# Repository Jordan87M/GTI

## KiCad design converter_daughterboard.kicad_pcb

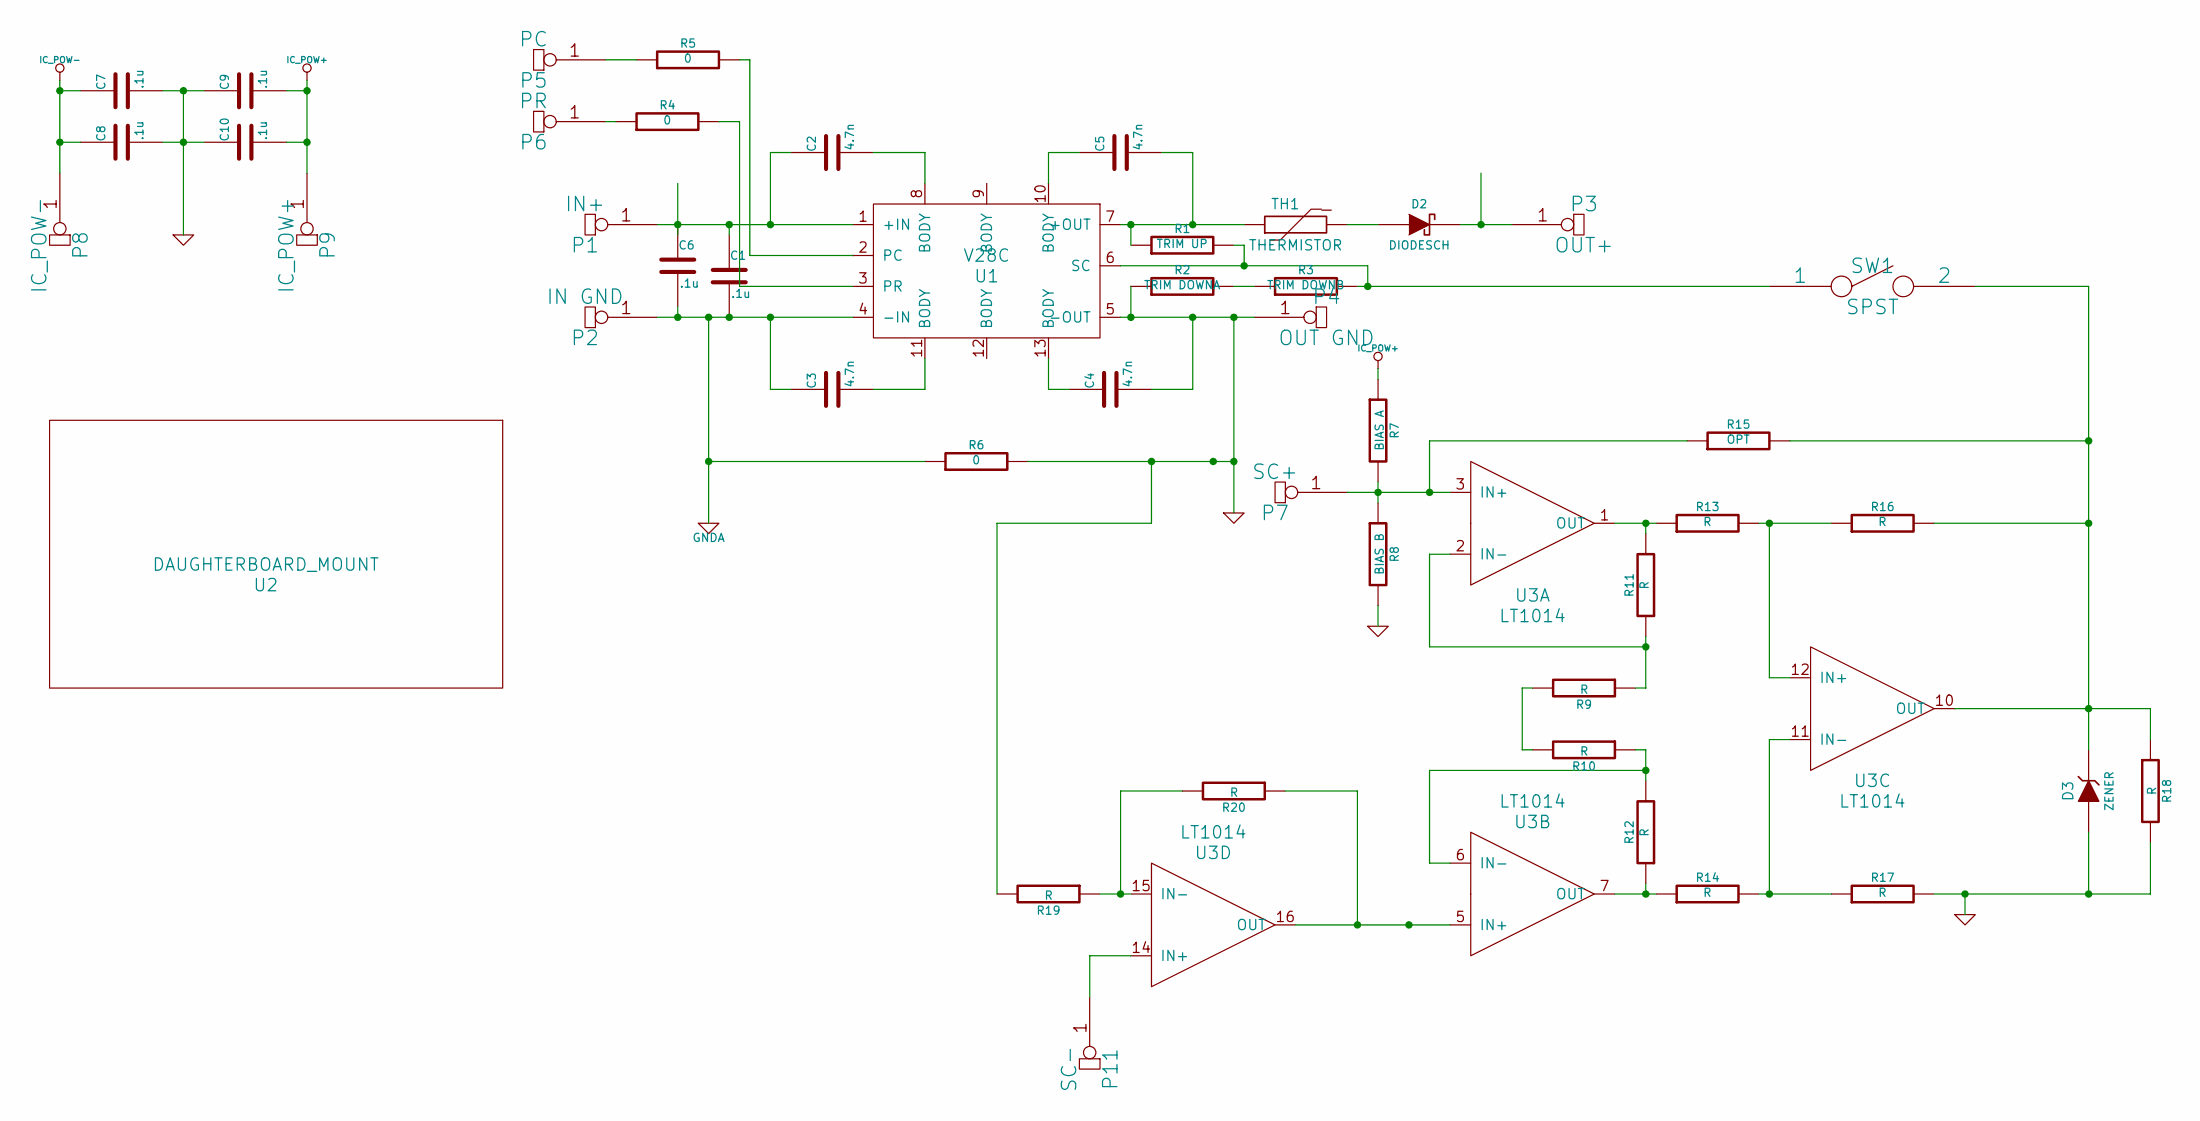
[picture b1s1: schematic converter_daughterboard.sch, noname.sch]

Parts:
C1, C6, C7, C8, C9, C10: .1u
C2, C3, C4, C5: 4.7n
D2: DIODESCH
D3: ZENER
P1: IN+
P2: IN GND
P3: OUT+
P4: OUT GND
P5: PC
P6: PR
P7: SC+
P8: IC_POW-
P9: IC_POW+
P11: SC-
R1: TRIM UP
R2: TRIM DOWNA
R3: TRIM DOWNB
R4, R5, R6: 0
R7: BIAS A
R8: BIAS B
R9, R10, R11, R12, R13, R14, R16, R17, R18, R19, R20: R
R15: OPT
SW1: SPST
TH1: THERMISTOR
U1: V28C
U2: DAUGHTERBOARD_MOUNT
U3: LT1014

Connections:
GND: C4.2, C7.2, C8.2, C9.1, C10.1, D3.1 (A), P4.1, R2.1, R6.2, R8.2, R17.2, R18.2, R19.2, U1.5 (-OUT)
GNDA: C1.2, C3.1, C6.2, P2.1, R6.1, U1.4 (-IN)
IC_POW+: C9.2, C10.2, P9.1, R7.1, U3.4 (IC_POW+)
IC_POW-: C7.1, C8.1, P8.1, U3.13 (IC_POW-)
unnamed: R14.2, R17.1, U3.11 (IN-)
unnamed: R11.2, R13.1, U3.1 (OUT)
unnamed: R9.1, R11.1, U3.2 (IN-)
unnamed: R10.1, R12.2, U3.6 (IN-)
unnamed: R12.1, R14.1, U3.7 (OUT)
unnamed: R9.2, R10.2
unnamed: R13.2, R16.1, U3.12 (IN+)
unnamed: D3.2 (K), R15.2, R16.2, R18.1, SW1.2, U3.10 (OUT)
unnamed: R19.1, R20.2, U3.15 (IN-)
unnamed: P11.1, U3.14 (IN+)
unnamed: P7.1, R7.2, R8.1, R15.1, U3.3 (IN+)
unnamed: R20.1, U3.5 (IN+), U3.16 (OUT)
unnamed: C3.2, U1.11 (BODY)
unnamed: C2.2, U1.8 (BODY)
unnamed: C4.1, U1.13 (BODY)
unnamed: R1.2, R3.2, SW1.1, U1.6 (SC)
unnamed: R2.2, R3.1
unnamed: C5.1, U1.10 (BODY)
unnamed: C5.2, R1.1, TH1.1, U1.7 (+OUT)
unnamed: R4.2, U1.3 (PR)
unnamed: R5.2, U1.2 (PC)
unnamed: P5.1, R5.1
unnamed: P6.1, R4.1
unnamed: D2.1 (A), TH1.2
unnamed: D2.2 (K), P3.1
unnamed: C1.1, C2.1, C6.1, P1.1, U1.1 (+IN)

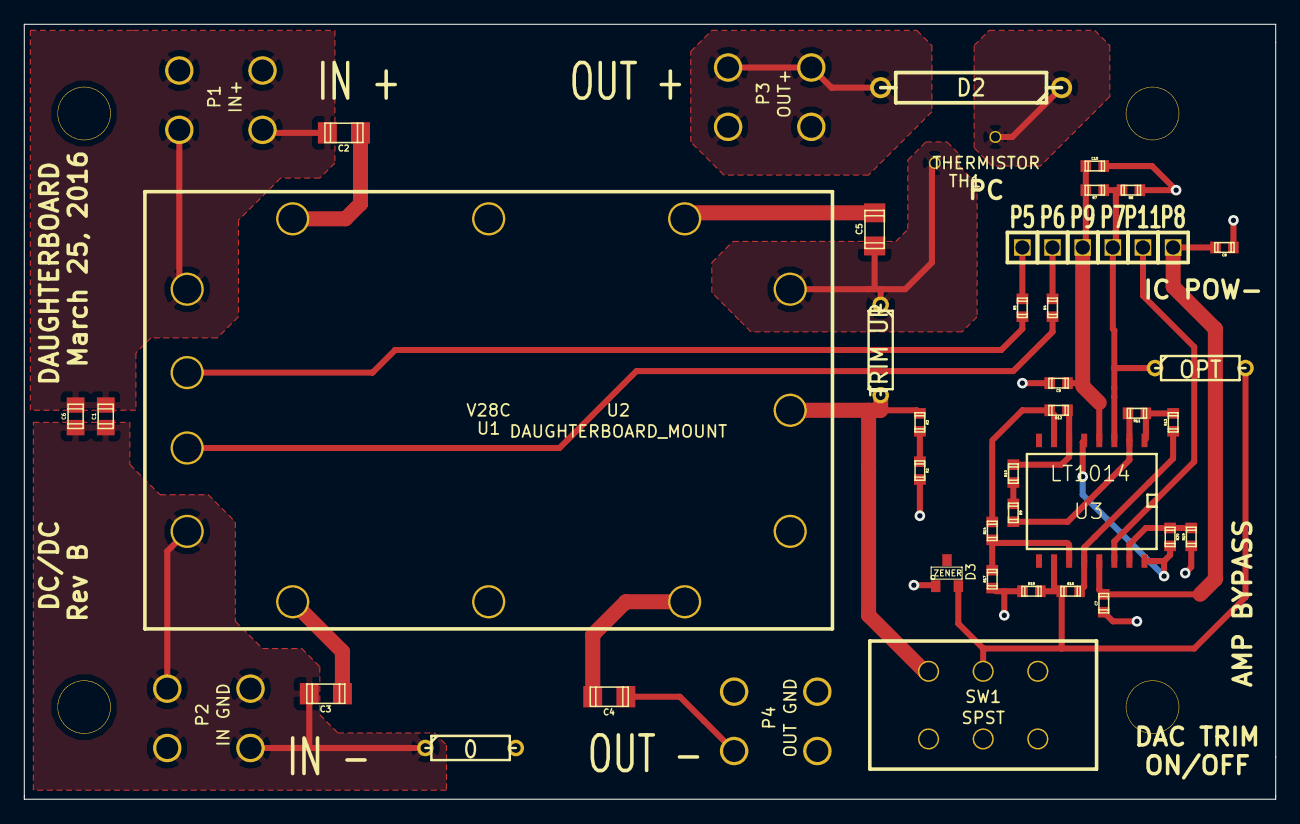
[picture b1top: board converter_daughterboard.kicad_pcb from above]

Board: 2 copper layers, 105.4 x 65.3 mm, 47 parts (0 on the bottom side), 30 nets.

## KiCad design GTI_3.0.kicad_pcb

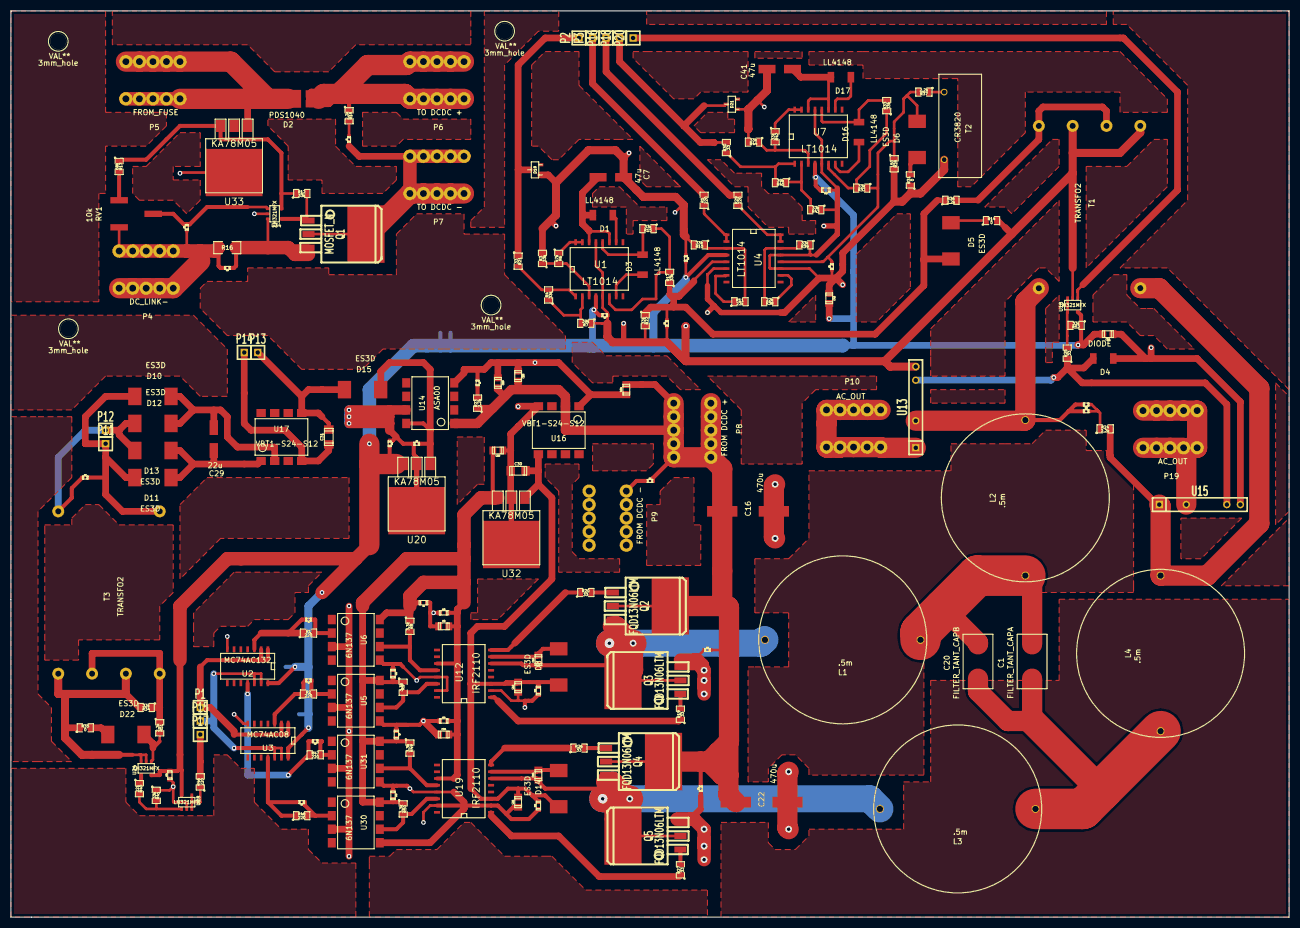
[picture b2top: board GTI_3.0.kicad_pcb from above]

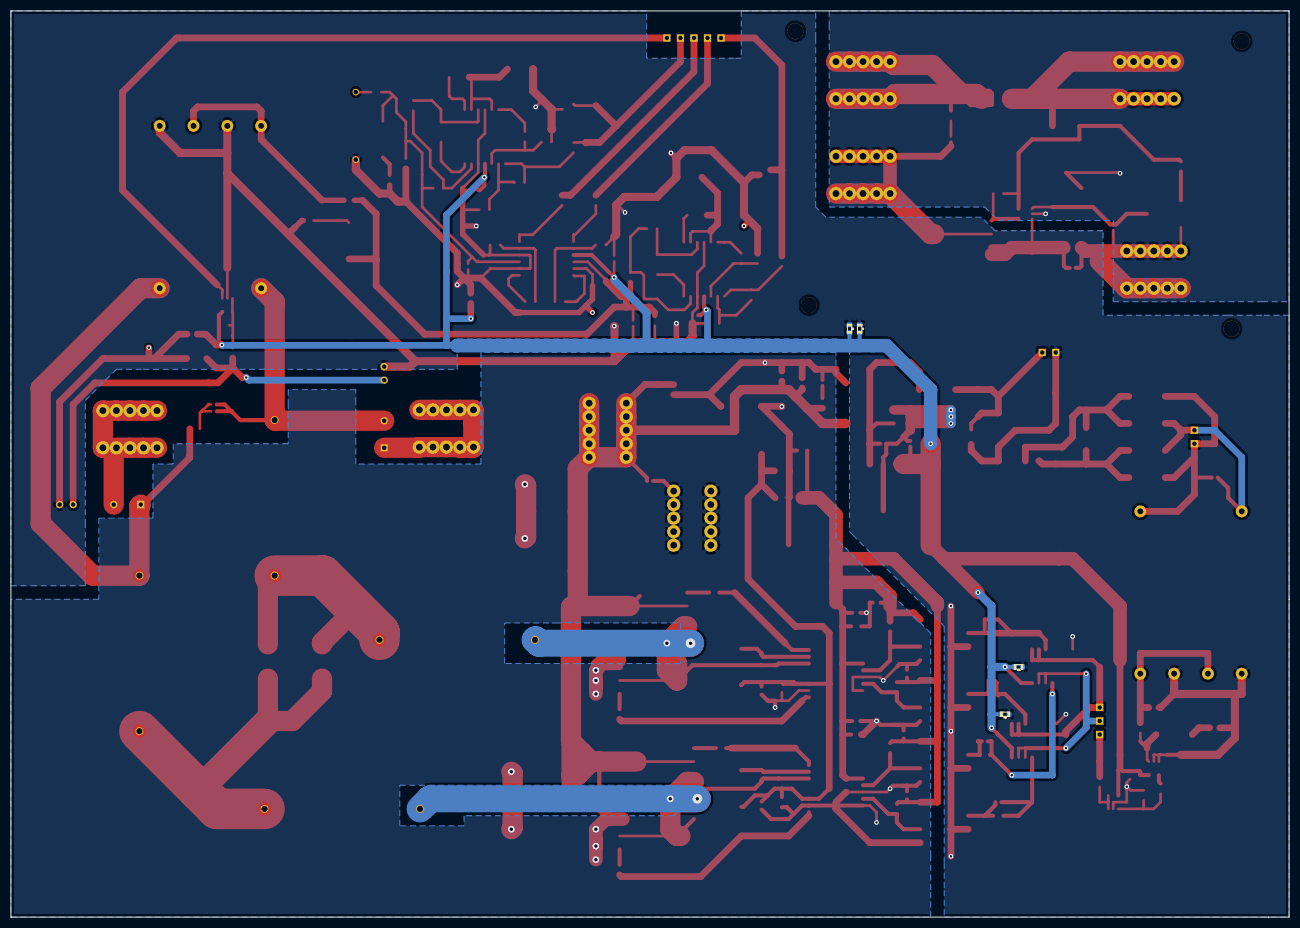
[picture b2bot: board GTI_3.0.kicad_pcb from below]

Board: 2 copper layers, 240.0 x 170.2 mm, 185 parts (4 on the bottom side), 98 nets.

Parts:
3mm_hole, 3mm_hole#2, 3mm_hole#3, 3mm_hole#4: VAL**; 3mm_hole
C1: FILTER_TANT_CAPA; 7343-31
C2, C3, C46, C47: 1n; c_0402
C4, C5, C6, C8, C10, C15, C25, C35, C42, C43, C44, C48, C49, C51: .1u; c_0603
C7, C41: 47u; PANASONIC_SMT_CAP_D
C9, C13, C14, C19, C23, C24, C26, C28, C33, C36, C45, C54: .47u; c_0805
C12, C34, C37: 10n; c_0402
C16, C22: 470u; PANASONIC_SMT_CAP_H
C17, C18, C21, C27, C32, C40, C50, C52, C53: .1u; c_0402
C20: FILTER_TANT_CAPB; 7343-31
C29: 22u; PANASONIC_SMT_CAP_C
C30, C31: .33u; c_1206
D1, D3, D16, D17: LL4148; SOD-80
D2: PDS1040; POWERDI5
D4: DIODE; SOD-80
D5, D6, D8, D10, D11, D12, D13, D14, D15, D22: ES3D; SMC
D7, D9, D19, D20: LNJ247W82RA; c_0402
D18, D21: BZX84C3V3; sot23
L1, L2, L3, L4: .5m; Bourns_High_Current_Choke
P1: HIGH_FREQ_PWM; SIL-1
P2: OUTPUTV_PEAK; SIL-1
P3: OUTPUTV_EDGE_DET; SIL-1
P4: DC_LINK-; Screw_TerminalA
P5: FROM_FUSE; Screw_TerminalA
P6: TO DCDC +; Screw_TerminalA
P7: TO DCDC -; Screw_TerminalA
P8: FROM DCDC +; Screw_TerminalA
P9: FROM DCDC -; Screw_TerminalA
P10, P19: AC_OUT; Screw_TerminalA
P11: GRID REF +; SIL-1
P12: GRID REF -; SIL-1
P13: EVK_POW+; SIL-1
P14: EVK_POW-; SIL-1
P15: LOW_FREQ_PWM; SIL-1
P16: OUTPUTI_EDGE_DET; SIL-1
P17: REF_EDGE_DET; SIL-1
P18: OUTPUTI_PEAK; SIL-1
P20: DIS/CONN; SIL-1
Q1: MOSFET_N; TO263
Q2, Q3, Q4, Q5: FQD13N06LTM; TO263
R1, R2, R5, R29, R46, R47, R48: 220; SM0805
R3, R4, R10, R12, R15, R17, R22, R32, R33, R34, R39, R41, R42, R43, R44, R52: 33k; SM0805
R6: 47k; SM0805
R7, R45: 39k; SM0805
R8, R9, R49, R50: 3.3k; SM0805
R11, R38, R40: 22k; SM0805
R13: 68k; SM0805
R14, R31, R35: 0; SM0805
R16: .01; SM1206
R18, R23, R24, R36, R37, R51: 2.2k; SM0805
R19, R20, R21, R25, R26, R27, R30: 33; SM0805
R28: 150; SM0805
RV1: 10k; Bourns_3361
T1, T3: TRANSFO2; Tamura_3FS
T2: CR3820; CR3800_XFMR
U1, U4, U7: LT1014; SO16W
U2: MC74AC132; SO14N
U3: MC74AC08; SO14N
U5, U6, U30, U31: 6N137; 8-DIP_SMT
U12, U19: IRF2110; SO16W
U13, U15: SSR; SSRfromSIL7
U14: ASA00; 8-DIP_SMT
U16, U17: VBT1-S24-S12; 8-DIP_SMT
U18, U24, U28, U34: LM321MFX; SOT23-5
U20, U32, U33: KA78M05; DPAK3

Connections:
+5V: C4.1, C5.1, C9.1, C10.1, C33.1, C35.1, C36.1, C48.1, C49.1, R8.1, R9.1, R49.1, R50.1, U5.8, U6.8, U12.11, U19.11, U30.8, U31.8, U32.3
+5VA: C6.1, C8.1, C32.1, C40.1, C42.1, C43.1, C44.1, C45.1, C50.1, C51.1, C54.1, R52.1, U1.4, U2.14, U3.14, U4.4, U7.4, U18.5, U20.3, U24.5, U28.5
+12V: C14.1, C15.1, C25.1, C26.1, C27.1, C30.1, C31.1, D8.1, D14.1, D15.1, D15.2, P13.1, U12.3, U14.8, U16.5, U17.5, U19.3, U20.1, U32.1
+24V: C16.1, C17.1, C18.1, C19.1, C21.1, C22.1, C23.1, C24.1, P8.1, Q2.2, Q4.2, R23.1, U14.1, U16.2
/DClinkGND: C53.2, Q1.3, R16.2, U34.3
GND: C4.2, C5.2, C9.2, C10.2, C14.2, C15.2, C16.2, C17.2, C18.2, C19.2, C21.2, C22.2, C23.2, C24.2, C25.2, C26.2, C30.2, C33.2, C35.2, C36.2, C48.2, C49.2, D9.2, P9.1, Q3.3, Q5.3, U5.5, U6.5, U12.2, U12.13, U12.15, U14.4, U16.1, U16.4, U19.2, U19.13, U19.15, U30.5, U31.5, U32.2
GNDA: C6.2, C7.2, C8.2, C12.2, C27.2, C31.2, C32.2, C34.2, C40.2, C41.2, C42.2, C43.2, C44.2, C45.2, C50.2, C51.2, C54.2, D4.1, D18.1, D21.1, P14.1, R3.2, R7.1, R10.2, R14.2, R22.2, R28.2, R31.1, R34.2, R35.1, R39.1, R41.1, R43.1, R44.2, T1.6, T1.8, T2.2, T3.6, T3.8, U1.5, U1.13, U2.7, U3.7, U4.6, U4.11, U4.13, U5.3, U6.3, U7.5, U7.13, U13.7, U14.7, U15.7, U17.4, U18.2, U20.2, U24.2, U24.3, U28.2, U30.3, U31.3
unnamed: Q4.1, R26.2
unnamed: Q5.1, R27.2
unnamed: Q3.1, R19.2
unnamed: Q2.1, R20.2
unnamed: R8.2, U6.6, U12.12
unnamed: R9.2, U5.6, U12.14
unnamed: C29.1, D10.2, D12.2, U17.2
unnamed: D1.1, U1.10
unnamed: R29.1, U4.15, U4.16
unnamed: R46.1, U28.3, U28.4
unnamed: R40.1, U24.4
unnamed: R40.2, R41.2, U28.1
unnamed: R11.1, U4.7
unnamed: R38.2, R39.2, U4.14
unnamed: R38.1, U4.10
unnamed: R43.2, R45.1, U7.2
unnamed: C29.2, D11.1, D13.1, U17.1
unnamed: R32.2, R33.1, U7.6
unnamed: R49.2, U19.12, U31.6
unnamed: R20.1, U12.8
unnamed: R19.1, U12.1
unnamed: R50.2, U19.14, U30.6
unnamed: R26.1, U19.8
unnamed: R27.1, U19.1
unnamed: R5.1, U4.1, U4.2
unnamed: D3.1, U1.7
unnamed: P3.1, R5.2
unnamed: P17.1, R46.2
unnamed: D7.2, P7.1, Q1.2
unnamed: D7.1, R18.2
unnamed: D2.2, P6.1, R18.1
unnamed: D9.1, R23.2
unnamed: R4.2, R21.2, U1.1
unnamed: R3.1, R6.2, U1.3
unnamed: P19.1, U15.3
unnamed: P10.1, U13.1
unnamed: R4.1, R7.2, U1.2
unnamed: Q1.1, R12.2, U34.4
unnamed: R36.2, T1.5, T1.7
unnamed: R30.1, R45.2, U7.1
unnamed: R42.2, R44.1, U7.3
unnamed: D17.1, U7.10
unnamed: R6.1, U1.15, U1.16
unnamed: C7.1, D1.2, U1.11, U1.14
unnamed: D3.2, R15.2, U1.12
unnamed: R15.1, R17.2, U1.6
unnamed: D5.1, R14.1
unnamed: D22.2, R51.2, U24.1
unnamed: D6.1, R31.2
unnamed: R37.1, T2.1
unnamed: C12.1, D5.2, R17.1, R22.1, R36.1, U4.5
unnamed: D22.1, R35.2
unnamed: R34.1, R51.1, T3.5, T3.7
unnamed: R25.2, R52.2, U18.3, U18.4
unnamed: P20.1, U18.1
unnamed: C34.1, D6.2, R28.1, R32.1, R37.2, U4.12
unnamed: R13.2, RV1.1
unnamed: D21.2, P18.1, R30.2
unnamed: P16.1, R29.2
unnamed: D18.2, P2.1, R21.1
unnamed: D19.1, D20.2, L2.2, T1.1, U13.3
unnamed: C1.1, C20.1, L1.1, L2.1
unnamed: C1.2, C20.2, L3.1, L4.1
unnamed: L4.2, R24.2, T1.4, U15.1
unnamed: C41.1, D17.2, U7.11, U7.14
unnamed: D16.2, R33.2, U7.12
unnamed: D16.1, U7.7
unnamed: R42.1, U7.15, U7.16
unnamed: C52.1, RV1.2, U34.1
unnamed: D4.2, R25.1, U13.6, U15.6
unnamed: C52.2, C53.1, P4.1, R16.1, RV1.3, U33.2, U34.2
unnamed: R12.1, R13.1, U33.3, U34.5
unnamed: D2.1, P5.1, U33.1
unnamed: P15.1, U2.12, U2.13, U3.12, U3.13
unnamed: P1.1, U2.1, U2.2, U3.1, U3.2
unnamed: C13.2, L1.2, Q2.3, Q3.2, U12.6
unnamed: C28.2, L3.2, Q4.3, Q5.2, U19.6
unnamed: R10.1, R11.2, U4.3
unnamed: C28.1, D14.2, U19.7
unnamed: C13.1, D8.2, U12.7
unnamed: C47.2, R48.2, U30.2
unnamed: C37.2, D12.1, D13.2, P12.1, T3.4
unnamed: C37.1, D10.1, D11.2, P11.1, T3.1
unnamed: C3.2, R2.2, U5.2
unnamed: C46.2, R47.2, U31.2
unnamed: C46.1, R47.1, U2.11
unnamed: C2.2, R1.2, U6.2
unnamed: C2.1, R1.1, U2.3
unnamed: C3.1, R2.1, U3.3
unnamed: C47.1, R48.1, U3.11
unnamed: D19.2, D20.1, R24.1

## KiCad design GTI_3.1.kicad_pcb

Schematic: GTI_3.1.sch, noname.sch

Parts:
C1, C2, C13, C20, C117: 22p
C3, C4, C10, C11, C15, C16, C19, C23, C31, C44, C103, C104, C105, C106: 33n
C5, C56, C87: 4.7u
C6, C7, C21, C113: 2.2u
C8, C12, C14, C17, C22, C24, C25, C26, C30, C32, C34, C37, C39, C40, C42, C48, C49, C50, C51, C54, C57, C61, C64, C68, C72, C82, C86, C89, C91, C92, C93, C94, C97, C98, C107, C108, C109, C110, C111, C118, C120, C121, C122, C123, C124, C125: .1u
C9: 470p
C18, C99, C100, C101, C102: 2.7n
C27: 22u
C28, C59, C60, C65, C74, C76, C80, C83, C84: .47u
C29, C58, C85, C88, C116: 10n
C33, C52, C90, C119: 47u
C35, C70, C73, C78, C79: 10u
C36, C38, C41, C43, C127: CSNUB
C45, C112: 1u
C46, C47, C95, C96: DNS
C53: CP1
C55: C
C62, C69: 470u
C63: 120u
C66, C67: NP_FILTER_CAP
C71, C77, C114, C115, C126, C128: 1n
C75: 100u
C81: .33u
D1: TVS
D2: MBRS340T3G
D3, D11, D22, D23, D24, D25: BZX84C3V3
D4, D20, D21: STPS1L20MF
D5, D7, D9, D10, D18, D19: LL4148
D6, D8, D12, D14: ES3D
L1: MSS1278 15u
L2, L3, L4, L5: .5m
L6: 4.7u
L7: 56uH
L8: 4.7uH
P1: PROGRAM_INT
P2: SPI1 SCK
P3: SPI1 MOSI
P4: SPI1 MISO
P5: SPI1_CS2
P6: HIGH_FREQ_PWM
P7: OUTPUTV_PEAK
P8: OUTPUTV_EDGE_DET
P9: FROM_FUSE
P10: DC_LINK-
P11: GNDB_TEST_#1
P12: BRD_DC_LINK+
P13: BRD_DC_LINK-
P14: TO DCDC +
P15: TO DCDC -
P16: FROM DCDC +
P17: FROM DCDC -
P18, P27: AC_OUT
P19: OUTPUT_INDICATOR_A
P20: BRD_DC_RAIL+
P21: BRD_DC_RAIL-
P22: OUTPUT_INDICATOR_B
P23: GRID REF +
P24: GRID REF -
P25: DIS/CONN OUT
P26: BRD_GRID_REF+
P28: DIS/CONN IN
P29: BRD_GRID_REF-
P30: DIS/CONN_TEST
P31: GNDA_TEST_#1
P32: LOW_FREQ_PWM
P33: OUTPUTI_EDGE_DET
P34: REF_EDGE_DET
P35: OUTPUTI_PEAK
P36: BACKLIGHT_5V
P37: 5V_SOURCE_RELAY_SUPPLY
P38: 5V_SOURCE_RELAY_RETURN
P39: RESET_N
P40: GNDA
P41: VCC3_3
P42: ALT_VOLTAGE_MEAS
P43: ALT_CURRENT_MEAS
P44: ALT_REF
P45: PWM_BRIGHTNESS
P46: ALT_MEAS_12VA
P47: ALT_MEAS_GNDA
P48, P49: CONNECTOR
Q1: DMN6075
Q2, Q3, Q4, Q5: FQD13N06LTM
R1, R41, R65, R67, R95: 10k
R2, R34, R35, R42, R45, R47, R51, R54, R58, R59, R61, R62, R64, R66, R68, R69, R71, R86, R88, R89, R90: 33k
R3, R8, R9, R12, R18, R19, R83: 2.2k
R4, R7, R17, R20: 1M
R5, R32, R33, R36, R70, R73, R75, R76: 220
R6: 1.5k
R10, R11, R13, R15: RSNUB
R14: 4.7k
R16, R57: 150
R21, R23: 4.7
R22: 18
R24, R25, R27, R30: 51
R26, R28, R29, R39, R40, R43, R44, R46, R60, R77, R78, R87: 3.3k
R31, R53, R74, R92: 33
R37, R98: 47k
R38, R72, R91: 39k
R48, R49, R55, R56, R96: 22
R50, R63: 1k
R52: MIN_LOAD
R79, R80: 39
R81, R82: 100
R84, R85: 56k
R93: 30k
R94: 330
R97: DNS
RV1: 10k
SW1: SPDT_RELAY
SW2: PANASONIC_DE2A-12V
T1, T3: TRANSFO2
T2: CR3820
TH1: PTC
U1: DAUGHTERBOARD_MOUNT
U2: AT32UC3A
U3: 50MHZCFPS73
U4: DP83848I
U5: LMS8117ADTX-3.3
U6: MICRO_USB_B
U7: LM2678SD-5.0
U8: J3026G01DNLT
U9: PQD6-Q24-D12
U10: LMT87
U11: MC74AC132
U12: MC74AC08
U13, U17, U20, U30: LT1014
U14, U15, U33, U34: 6N137
U16, U25, U31, U32: LM321MFX
U18: TLV3401
U19, U27: IRF2110
U21: MC74HC1G32
U22: PQMC1-S24-S12
U23: SN74AHC
U28, U29: KA78M05
VR1, VR2, VR3: VR
X1: CRYSTAL
X2: CRYSTAL_32K

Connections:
+5V: C48.1, C49.1, C56.1, C57.1, C83.1, C86.1, C87.1, C97.1, C98.1, R39.1, R40.1, R77.1, R78.1, U14.8 (Vcc), U15.8 (Vcc), U19.11 (Vdd), U27.11 (Vdd), U29.3 (OUT), U33.8 (Vcc), U34.8 (Vcc)
+5VA: C50.1, C80.1, C82.1, C84.1, C118.1, U10.1 (Vdd), U11.14 (+5VA), U12.14 (+5VA), U28.3 (OUT)
+12V: C60.1, C61.1, C72.1, C74.1, C75.1, D8.1 (A), D14.1 (A), R60.1, U19.3 (VCC), U22.6 (V_out_+), U27.3 (VCC), U29.1 (IN)
+12VA: C51.1, C54.1, C78.2, C89.1, C91.1, C92.1, C93.1, C94.1, C115.2, C120.1, C123.1, D6.1 (A), P46.1, R28.1, R93.1, R96.1, R97.1, SW2.1, U9.3 (Vo), U13.4 (+12VA), U16.5 (+), U17.4 (+12VA), U18.5 (Vdd), U20.4 (+12VA), U25.5 (+), U30.4 (+12VA), U31.5 (+), U32.5 (+)
+12VEVK: C27.1, C28.1, C81.1, D6.2 (K), U7.2 (VIN1), U7.3 (VIN2)
+24V: C62.1, C64.1, C65.1, C68.1, C69.1, C70.1, L6.1, L7.1, P16.1, Q2.2 (D), Q4.2 (D), R10.1, R13.1, R44.1, R98.1, VR1.1
-12VA: C8.1, C17.1, C25.1, C79.2, C114.2, C122.1, R26.2, U9.5 (-Vo), U13.13 (-12VA), U17.13 (-12VA), U20.13 (-12VA), U30.13 (-12VA)
GND: C48.2, C49.2, C56.2, C57.2, C60.2, C61.2, C62.2, C63.2, C64.2, C65.2, C68.2, C69.2, C70.2, C71.1, C72.2, C73.2, C74.2, C75.2, C77.1, C83.2, C86.2, C87.2, C97.2, C98.2, C112.2, C113.2, C114.1, C126.2, C128.2, D1.1 (A), P11.1, P17.1, P21.1, Q3.3 (S), Q5.3 (S), R4.2, R7.2, R11.2, R15.2, R17.2, R20.2, R60.2, R98.2, U9.1 (V_in_-), U14.5 (GND), U15.5 (GND), U19.2 (COM), U19.13 (SD), U19.15 (Vss), U22.1 (V_in_-), U22.7 (V_out_-), U27.2 (COM), U27.13 (SD), U27.15 (Vss), U29.2 (GND), U33.5 (GND), U34.5 (GND), VR1.2
GNDA: C1.2, C2.2, C3.2, C4.1, C5.1, C6.2, C7.2, C8.2, C9.2, C10.2, C11.2, C12.1, C13.2, C14.1, C15.2, C16.1, C17.2, C18.1, C19.1, C20.2, C21.1, C22.1, C23.1, C24.2, C25.2, C26.1, C27.2, C28.2, C30.1, C31.2, C32.2, C33.2, C34.2, C35.2, C37.2, C39.2, C40.2, C42.2, C44.2, C45.2, C50.2, C51.2, C52.2, C54.2, C58.2, C71.2, C77.2, C78.1, C79.1, C80.2, C81.2, C82.2, C84.2, C85.2, C89.2, C90.2, C91.2, C92.2, C93.2, C94.2, C99.2, C100.2, C101.2, C102.2, C103.2, C104.2, C105.2, C106.2, C107.2, C108.2, C109.2, C110.2, C111.2, C116.2, C117.2, C118.2, C119.2, C120.2, C121.2, C122.2, C123.2, C124.2, C125.2, D2.1 (A), D3.1 (A), D4.1 (A), D11.1 (A), D20.1 (A), D21.1 (A), D22.1 (A), D23.1 (A), D24.1 (A), D25.1 (A), P31.1, P40.1, P47.1, P48.1, P49.1, Q1.2 (S), R8.2, R9.2, R12.2, R22.1, R26.1, R28.2, R34.2, R38.1, R41.2, R50.2, R51.1, R54.2, R57.2, R59.2, R63.2, R65.1, R67.1, R69.1, R71.2, R83.2, R84.2, R85.2, R87.2, R89.1, R90.2, R94.2, SW1.9 (COIL-), T1.6 (SB), T1.8 (SD), T2.2, T3.6 (SB), T3.8 (SD), U2.8 (GND), U2.18 (GND), U2.28 (GND), U2.37 (GND), U2.52 (GND), U2.72 (GND), U2.83 (GND/ANA), U2.94 (GND), U2.109 (GND), U2.117 (GND), U3.2 (GND), U4.15 (AGND), U4.19 (AGND), U4.35 (IOGND), U4.36 (DGND), U4.47 (IOGND), U5.1 (GND), U6.5 (GND), U6.6 (SHIELD1), U6.7 (SHIELD2), U6.8 (SHIELD3), U6.9 (SHIELD4), U7.9 (GND), U7.15 (PGND), U8.10 (GND), U8.13, U8.14, U9.4 (0V), U10.3 (GND), U11.7 (GNDA), U12.7 (GNDA), U13.2 (IN-), U13.6 (IN-), U13.11 (IN-), U14.3 (-), U15.3 (-), U16.2 (-), U17.5 (IN+), U18.2 (GND), U20.5 (IN+), U21.3 (GND), U23.3 (GND), U25.2 (-), U25.3 (V-), U28.2 (GND), U30.5 (IN+), U31.2 (-), U32.2 (-), U33.3 (-), U34.3 (-)
unnamed: U2.104 (PB06), U4.44 (RXD_1/PHYAD2)
unnamed: U2.90 (PB01), U4.2 (TX_EN)
unnamed: U2.96 (PB02), U4.3 (TXD_0)
unnamed: U2.98 (PB03), U4.4 (TXD_1)
unnamed: U2.102 (PB05), U4.43 (RXD_0/PHYAD1)
unnamed: U2.106 (PB07), U4.41 (RX_ER/MDIX_EN)
unnamed: R81.1, U4.28 (LED_LINK/AN0)
unnamed: R81.2, U8.2 (LED_Y_CAT)
unnamed: R82.1, U4.26 (LED_ACT/COL/AN_EN)
unnamed: R82.2, U8.11 (LED_G_CAT)
unnamed: C2.1, U2.125 (PC03), X1.2
unnamed: U2.111 (PB08), U4.31 (MD)
unnamed: R6.2, U2.113 (PB09), U4.30 (MDIO)
unnamed: R18.1, U4.21 (RESERVED)
unnamed: R3.2, U4.39 (RX_DV/MII_MODE)
unnamed: R19.1, U4.20 (RESERVED)
unnamed: R24.1, U4.17 (TD+), U8.3 (TD+)
unnamed: R16.2, R22.2
unnamed: C26.2, C30.2, C34.1, C35.1, U4.18 (PFBIN1), U4.23 (PFBOUT), U4.37 (PFBIN2)
unnamed: R30.1, U4.13 (RD-), U8.8 (RD)
unnamed: R8.1, U4.5 (TXD_2)
unnamed: R9.1, U4.6 (TXD_3/SNI_MODE)
unnamed: R12.1, U4.8 (TCK)
unnamed: R25.1, U4.16 (TD-), U8.4 (TD-)
unnamed: R27.1, U4.14 (RD+), U8.7 (RD+)
unnamed: R36.1, U16.3 (V-), U16.4 (out)
unnamed: R35.1, R38.2, U30.2 (IN-)
unnamed: R34.1, R37.2, U30.3 (IN+)
unnamed: D7.2 (K), R45.2, U30.12 (IN+)
unnamed: R45.1, R47.2, U30.6 (IN-)
unnamed: R68.1, U20.15 (IN-), U20.16 (OUT)
unnamed: D18.2 (K), R62.2, U20.12 (IN+)
unnamed: D18.1 (A), U20.7 (OUT)
unnamed: D20.2 (K), R64.2, R65.2, U31.1 (V+)
unnamed: R70.1, U31.3 (V-), U31.4 (out)
unnamed: R72.2, R74.1, U20.1 (OUT)
unnamed: R68.2, R71.1, U20.3 (IN+)
unnamed: D19.1 (A), U20.10 (OUT)
unnamed: C29.1, U7.4 (CB)
unnamed: C29.2, D2.2 (K), L1.1, U7.12 (SWITCH3), U7.13 (SWITCH2), U7.14 (SWITCH1)
unnamed: C1.1, U2.124 (PC02), X1.1
unnamed: C13.1, U2.86 (PC01), X2.1
unnamed: C20.1, U2.85 (PC00), X2.4
unnamed: P25.1, R53.1
unnamed: C88.2, P24.1, P29.1, T3.4 (AB)
unnamed: R73.1, U32.3 (V-), U32.4 (out)
unnamed: R79.1, U2.70 (DM)
unnamed: R80.1, U2.71 (DP)
unnamed: R80.2, U6.3 (D+)
unnamed: D25.2 (K), P33.1, R70.2, U2.40 (PX11)
unnamed: C73.1, U22.8 (CS)
unnamed: P38.1, SW1.2 (COIL+)
unnamed: C33.1, L1.2, R83.1, SW1.1 (NC), U7.7 (FB)
unnamed: R14.2, U4.24 (RBIAS)
unnamed: R14.1, R16.1
unnamed: P5.1, U2.64 (PA19)
unnamed: P4.1, U2.60 (PA17)
unnamed: P3.1, U2.58 (PA16)
unnamed: P2.1, U2.57 (PA15)
unnamed: P1.1, R2.1, U2.66 (PA20)
unnamed: P6.1, U2.39 (PA05), U11.1, U11.2, U12.1, U12.2
unnamed: D22.2 (K), P34.1, R73.2, U23.2 (B)
unnamed: U2.87 (PX20), U23.4 (out)
unnamed: P30.1, R59.1, U2.101 (PX26), U25.1 (V+)
unnamed: R5.2, U2.88 (PB00), U3.3 (OUT), U4.34 (X1)
unnamed: R79.2, U6.2 (D-)
unnamed: U2.50 (PA11), U6.4 (ID)
unnamed: C66.1, C67.1, L2.1, L3.1
unnamed: C128.1, R43.2, R52.2, SW2.5, T1.4 (AB), TH1.2, VR3.2
unnamed: R91.2, R92.1, U17.1 (OUT)
unnamed: P32.1, U2.46 (PX14), U11.12, U11.13, U12.12, U12.13
unnamed: C95.1, R75.1, U11.11
unnamed: C46.1, R32.1, U11.3
unnamed: C46.2, R32.2, U15.2 (+)
unnamed: C47.1, R33.1, U12.3
unnamed: C47.2, R33.2, U14.2 (+)
unnamed: C95.2, R75.2, U34.2 (+)
unnamed: C96.1, R76.1, U12.11
unnamed: C96.2, R76.2, U33.2 (+)
unnamed: R88.2, R90.1, U17.3 (IN+)
unnamed: R95.2, U18.1 (out), U21.1 (A)
unnamed: U21.4 (out), U23.1 (A)
unnamed: RV1.2, U18.4 (-)
unnamed: R93.2, RV1.3
unnamed: R94.1, RV1.1
unnamed: D12.2 (K), R97.2
unnamed: C127.1, R96.2
unnamed: R53.2, R54.1, U25.4 (out)
unnamed: U2.67 (PX19), U21.2 (B)
unnamed: P44.1, R58.1, R63.1, T3.5 (SA), T3.7 (SC), U13.5 (IN+)
unnamed: D11.2 (K), R92.2, U2.78 (PA26), U18.3 (+)
unnamed: D10.1 (A), U17.10 (OUT)
unnamed: C119.1, D10.2 (K), R87.1, U17.11 (IN-), U17.14 (IN+)
unnamed: D9.2 (K), R86.2, U17.12 (IN+)
unnamed: D9.1 (A), U17.7 (OUT)
unnamed: R88.1, U17.15 (IN-), U17.16 (OUT)
unnamed: C117.1, U2.73 (PA21), U10.2 (Vout)
unnamed: R58.2, R86.1, U17.6 (IN-)
unnamed: R89.2, R91.1, U17.2 (IN-)
unnamed: C90.1, D19.2 (K), R85.1, U20.11 (IN-), U20.14 (IN+)
unnamed: R61.2, R62.1, U20.6 (IN-)
unnamed: D21.2 (K), R66.2, R67.2, U32.1 (V+)
unnamed: R42.1, U13.10 (OUT)
unnamed: R64.1, U13.1 (OUT)
unnamed: R40.2, U14.6 (OUT), U19.14 (LIN)
unnamed: R69.2, R72.1, U20.2 (IN-)
unnamed: R66.1, U13.7 (OUT)
unnamed: D5.1 (A), U30.10 (OUT)
unnamed: C66.2, C67.2, L4.1, L5.1
unnamed: D3.2 (K), P7.1, R31.1, U2.75 (PA23)
unnamed: D23.2 (K), P35.1, R74.2, U2.80 (PA28)
unnamed: R31.2, R35.2, U30.1 (OUT)
unnamed: C85.1, P43.1, R57.1, R61.1, T2.1, U13.3 (IN+)
unnamed: R39.2, U15.6 (OUT), U19.12 (HIN)
unnamed: R49.1, U19.8 (HO)
unnamed: R55.1, U27.8 (HO)
unnamed: R56.1, U27.1 (LO)
unnamed: R48.1, U19.1 (LO)
unnamed: R78.2, U27.14 (LIN), U33.6 (OUT)
unnamed: R77.2, U27.12 (HIN), U34.6 (OUT)
unnamed: R37.1, U30.15 (IN-), U30.16 (OUT)
unnamed: C52.1, D5.2 (K), R84.1, U30.11 (IN-), U30.14 (IN+)
unnamed: D7.1 (A), U30.7 (OUT)
unnamed: C88.1, P23.1, R46.2, T3.1 (AA)
unnamed: C59.1, D8.2 (K), U19.7 (Vb)
unnamed: R21.2, U19.6 (Vs)
unnamed: P18.1, SW2.3
unnamed: R23.2, U27.6 (Vs)
unnamed: C76.1, D14.2 (K), U27.7 (Vb)
unnamed: D4.2 (K), R41.1, R42.2, U16.1 (V+)
unnamed: P12.1, R29.2
unnamed: P20.1, R44.2
unnamed: P22.1, R43.1
unnamed: P26.1, R46.1
unnamed: C115.1, L8.1, U9.2 (V_in_+)
unnamed: C63.1, C113.1, D1.2 (K), L7.2, L8.2
unnamed: P27.1, SW2.6
unnamed: C127.2, D12.1 (A), Q1.3 (D), SW2.8
unnamed: C41.1, R13.2
unnamed: C43.2, R15.1
unnamed: C41.2, C43.1, C76.2, L4.2, Q4.3 (S), Q5.2 (D), R23.1
unnamed: P37.1, SW1.10 (NO), U2.68 (VBUS), U6.1 (VBUS)
unnamed: Q4.1 (G), R17.1, R55.2
unnamed: Q2.1 (G), R7.1, R49.2
unnamed: Q5.1 (G), R20.1, R56.2
unnamed: U2.76 (PA24), U4.7 (PWR_DOWN/INIT)
unnamed: Q3.1 (G), R4.1, R48.2
unnamed: C38.2, R11.1
unnamed: C36.2, C38.1, C59.2, L2.2, Q2.3 (S), Q3.2 (D), R21.1
unnamed: C36.1, R10.2
unnamed: C40.1, P36.1, SW1.5 (COM), U5.3 (VIN)
unnamed: P39.1, R1.2, U2.23 (RESET_N), U4.29 (RESET_N)
unnamed: D24.2 (K), P8.1, R36.2, U2.26 (PX06)
unnamed: P45.1, U2.141 (PB18)
unnamed: L5.2, TH1.1
unnamed: C126.1, L3.2, P19.1, R52.1, SW2.4, T1.1 (AA), VR3.1
unnamed: C58.1, C116.1, P42.1, R47.1, R50.1, T1.5 (SA), T1.7 (SC), U13.12 (IN+)
unnamed: C53.1, C55.1, P9.1, P14.1, R29.1, VR2.1
unnamed: U2.134 (PB15), U4.40 (CRS/CRS_DV/LED_CFG)
unnamed: C112.1, L6.2, U22.2 (V_in_+)
unnamed: P28.1, Q1.1 (G), R51.2
unnamed: C53.2, C55.2, P10.1, P13.1, P15.1, VR2.2
VCC: C3.1, C4.2, C5.2, C10.1, C11.1, C12.2, C14.2, C15.1, C16.2, C22.2, C23.2, C24.1, C31.1, C32.1, C37.1, C39.1, C42.1, C44.1, C45.1, C107.1, C109.1, C110.1, C111.1, C121.1, C124.1, C125.1, P41.1, R1.1, R2.2, R3.1, R5.1, R6.1, R18.2, R19.2, R24.2, R25.2, R27.2, R30.2, R95.1, U2.7 (VDDIO), U2.17 (VDDIN), U2.36 (VDDIO), U2.69 (VDDIO), U2.81 (VDDANA), U2.82 (ADVREF), U2.92 (VDDIO), U2.93 (VDDIO), U2.108 (VDDIO), U2.116 (VDDIO), U3.4 (VCC), U4.22 (AVDD33), U4.32 (IOVDD33), U4.48 (IOVDD33), U5.2 (VOUT), U8.1 (LED_Y_AN), U8.5 (CT), U8.6 (CT), U8.12 (LED_G_AN), U21.5 (Vdd), U23.5 (Vdd)
VCC18: C6.1, C7.1, C9.1, C18.2, C19.2, C21.2, C99.1, C100.1, C101.1, C102.1, C103.1, C104.1, C105.1, C106.1, C108.1, U2.16 (VDDOUT), U2.29 (VDDCORE), U2.51 (VDDCORE), U2.55 (VDDCORE), U2.84 (VDDPLL), U2.138 (VDDCORE)

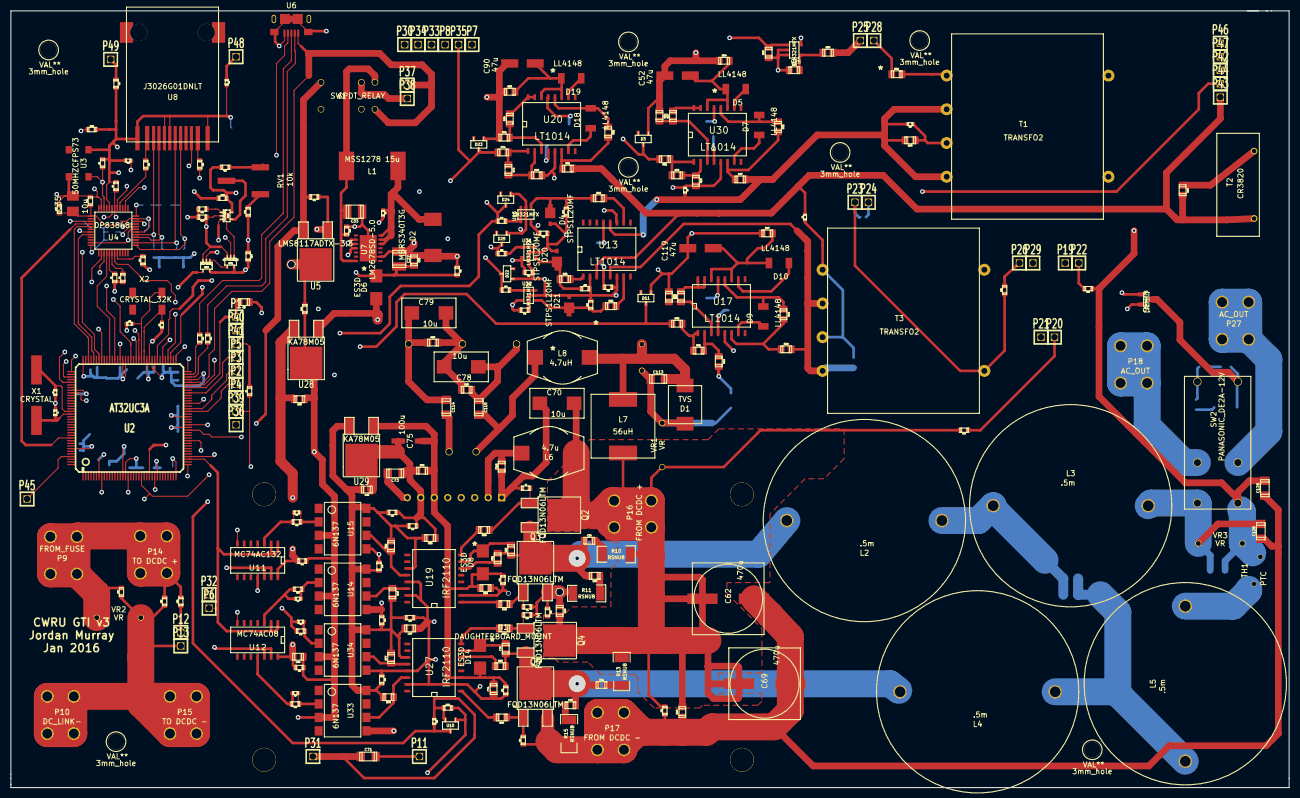
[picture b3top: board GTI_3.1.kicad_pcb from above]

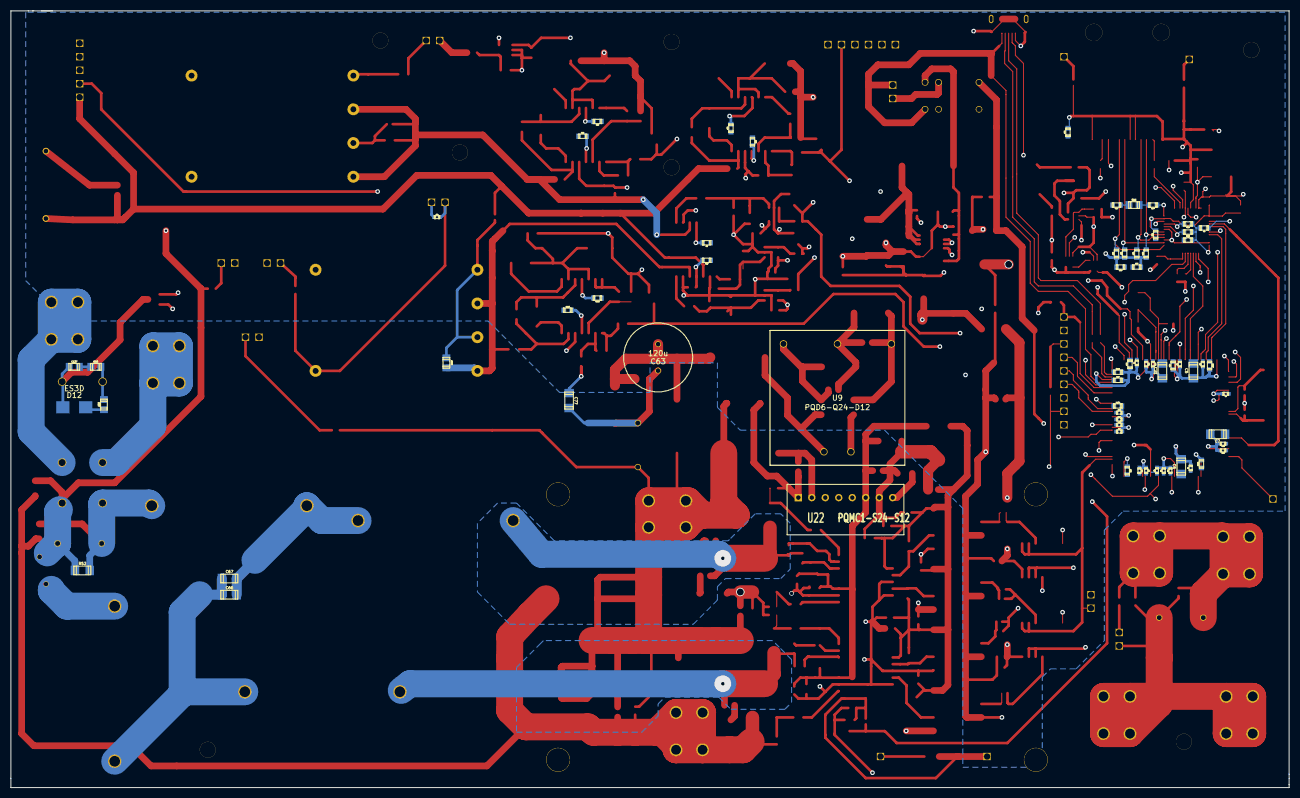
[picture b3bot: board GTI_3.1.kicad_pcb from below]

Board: 4 copper layers, 240.8 x 146.3 mm, 360 parts (66 on the bottom side), 173 nets.

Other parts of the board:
3mm_hole, 3mm_hole#2, 3mm_hole#3, 3mm_hole#4, 3mm_hole#5, 3mm_hole#6, 3mm_hole#7: VAL**; 3mm_hole

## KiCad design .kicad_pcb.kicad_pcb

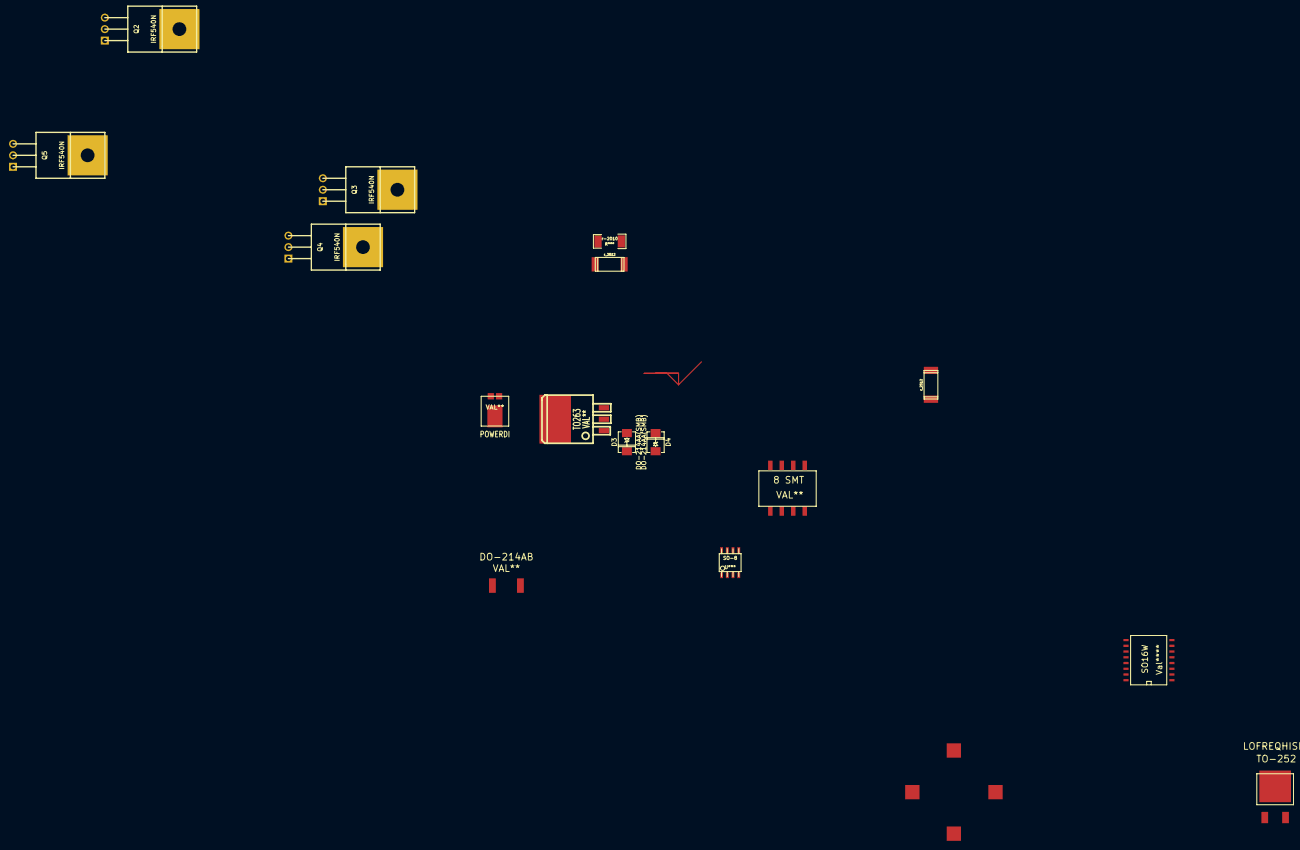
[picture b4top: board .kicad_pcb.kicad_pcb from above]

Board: 2 copper layers, 17 parts (0 on the bottom side), 4 nets.

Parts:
8 SMT: VAL**; 8 SMT
DO-214AA(SMB): D4; DO-214AA(SMB)
DO-214AA(SMB)#2: D3; DO-214AA(SMB)
DO-214AB: VAL**; DO-214AB
POWERDI: VAL**; POWERDI5
Q2, Q3, Q4, Q5: IRF540N; TO220
SO16W: Val****; SO16W
SO-8: U***; so-8
TO263: VAL**; TO263
TO-252: LOFREQHISIDE; TO-252
common mode choke: VAL**; CommModeChoke
r-2010: R***; r_2010
r_2512, r_2512#2: R***; r_2512

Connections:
GNDA: Q3.3, Q5.3
unnamed: Q2.3, Q3.1
unnamed: Q2.1, Q4.1
unnamed: Q4.3, Q5.1
